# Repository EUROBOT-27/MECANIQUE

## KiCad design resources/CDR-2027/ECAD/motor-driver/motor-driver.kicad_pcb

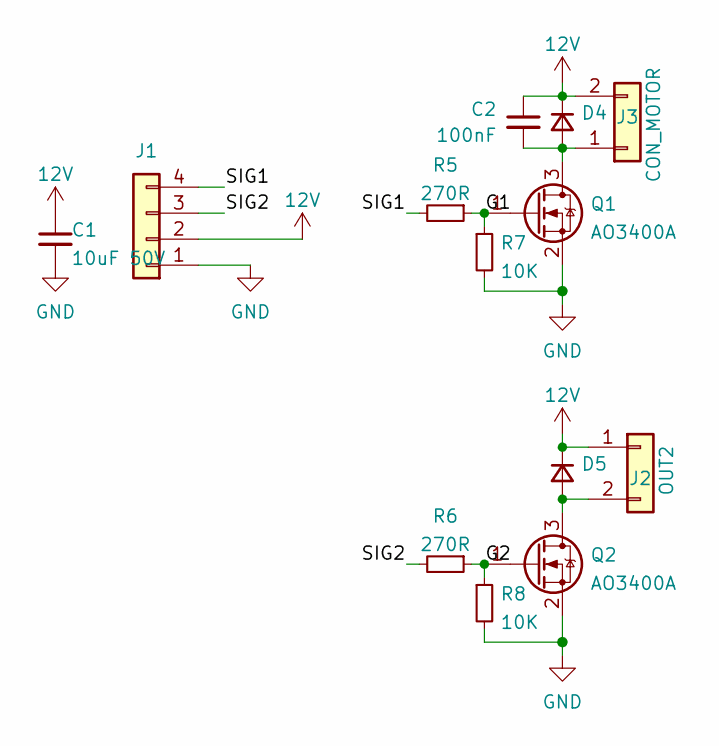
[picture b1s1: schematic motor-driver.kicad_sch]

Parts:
C1: 10uF 50V; C_1206_3216Metric; LCSC C13585
C2: 100nF; C_1206_3216Metric; LCSC C24497
D4, D5: SS34; D_SMA; LCSC C8678
J1: Conn_01x04; Molex_KK-254_AE-6410-04A_1x04_P2.54mm_Vertical
J2: OUT2; Molex_KK-254_AE-6410-02A_1x02_P2.54mm_Vertical
J3: CON_MOTOR; Moteur_Cosses_2xFente_3.6x2.2mm_R10.6mm
Q1, Q2: AO3400A; SOT-23; LCSC C20917
R5, R6: 270R; R_1206_3216Metric; LCSC C4466
R7, R8: 10K; R_1206_3216Metric; LCSC C17902

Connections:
12V: C1.1, C2.1, D4.1 (K), D5.1 (K), J1.2, J2.1, J3.2
/G1: Q1.1 (G), R5.1, R7.1
/G2: Q2.1 (G), R6.1, R8.1
/SIG1: J1.4, R5.2
/SIG2: J1.3, R6.2
GND: C1.2, J1.1, Q1.2 (S), Q2.2 (S), R7.2, R8.2
unnamed: C2.2, D4.2 (A), J3.1, Q1.3 (D)
unnamed: D5.2 (A), J2.2, Q2.3 (D)

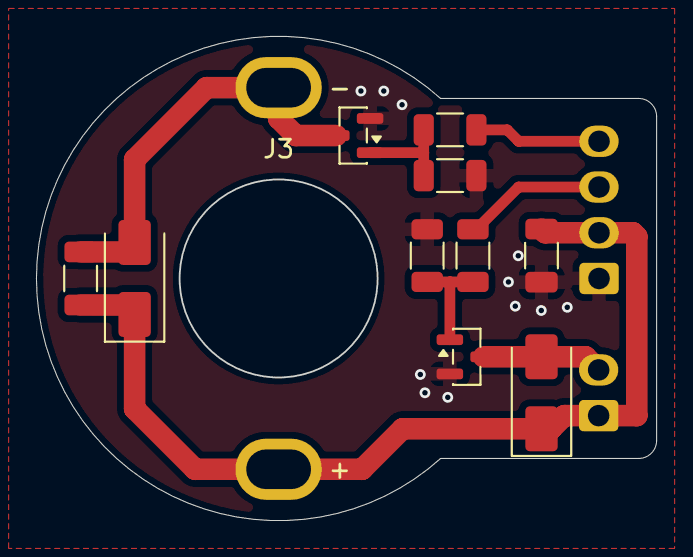
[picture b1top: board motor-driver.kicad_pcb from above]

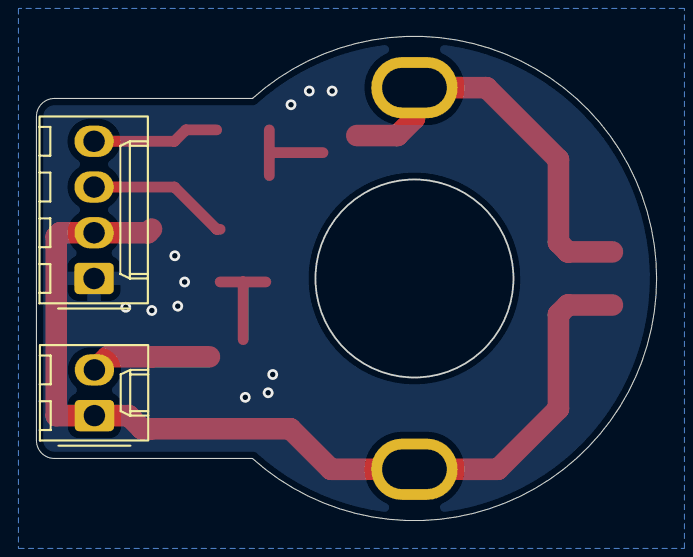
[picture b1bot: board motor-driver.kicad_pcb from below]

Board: 2 copper layers, 34.5 x 26.9 mm, 13 parts (2 on the bottom side), 8 nets.

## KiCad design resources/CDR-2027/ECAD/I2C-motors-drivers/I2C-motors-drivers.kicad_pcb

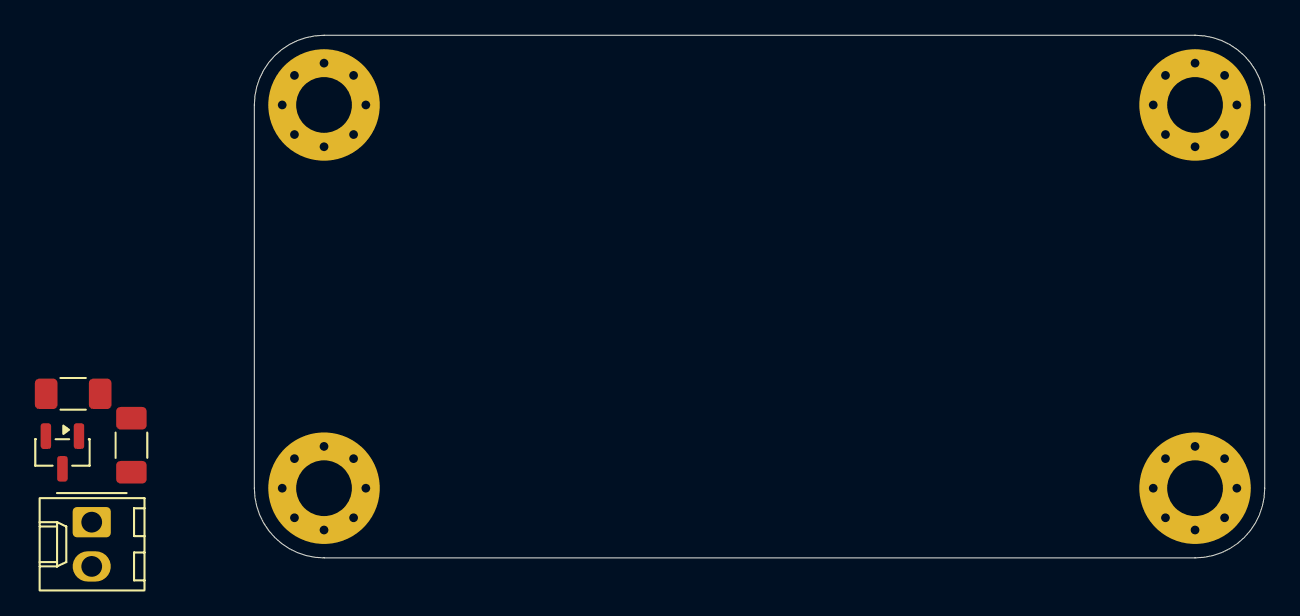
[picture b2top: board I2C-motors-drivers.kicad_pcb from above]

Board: 2 copper layers, 58.0 x 30.0 mm, 9 parts (1 on the bottom side), 4 nets, no tracks yet.

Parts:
D4: D_Small; D_SMA_Handsoldering
H1, H2, H3, H4: MountingHole_Pad_MP; MountingHole_3.2mm_M3_Pad_Via
J3: CON_EV; Molex_KK-254_AE-6410-02A_1x02_P2.54mm_Vertical
Q1: AO3400A; SOT-23
R5: 270R; R_1206_3216Metric_Pad1.30x1.75mm_HandSolder
R7: 10K; R_1206_3216Metric_Pad1.30x1.75mm_HandSolder

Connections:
12V: D4.1 (K), J3.2
GND: Q1.2 (S), R7.2
unnamed: D4.2 (A), J3.1, Q1.3 (D)
unnamed: Q1.1 (G), R5.1, R7.1

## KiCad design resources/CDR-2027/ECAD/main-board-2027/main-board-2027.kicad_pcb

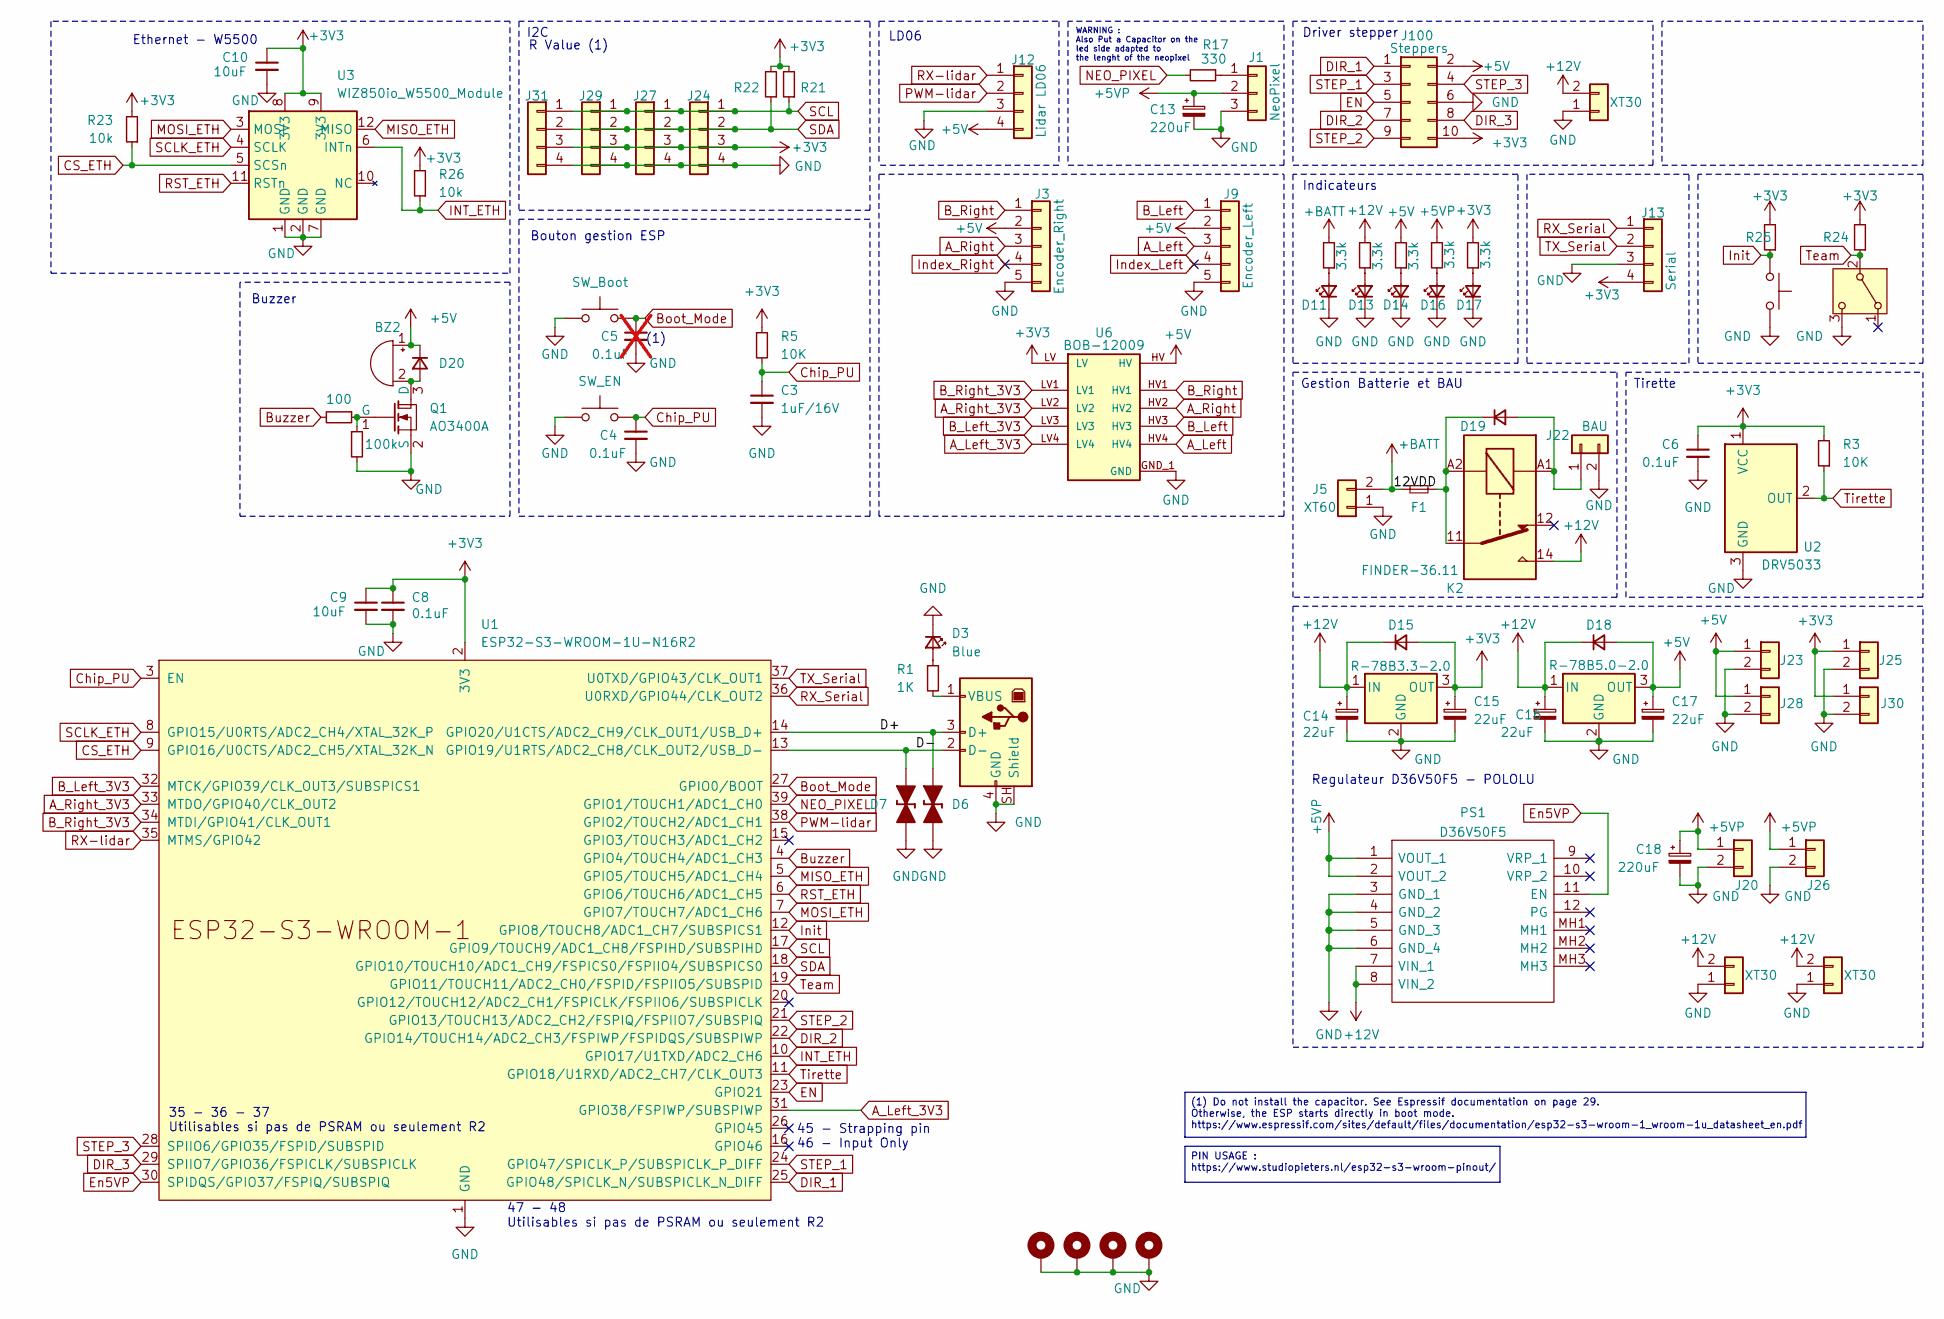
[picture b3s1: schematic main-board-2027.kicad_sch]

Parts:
BZ2: Buzzer; Buzzer_12x9.5RM7.6
C3: 1uF/16V; C_1206_3216Metric
C4: 0.1uF; C_1206_3216Metric
C5: 0.1uF; C_1206_3216Metric; not fitted
C6, C8: 0.1uF; C_1206_3216Metric_Pad1.33x1.80mm_HandSolder
C9, C10: 10uF; C_1206_3216Metric_Pad1.33x1.80mm_HandSolder
C13, C18: 220uF; CP_Radial_D8.0mm_P3.80mm
C14, C15, C16, C17: 22uF; CP_Elec_5x5.4
D3: Blue; LED_1206_3216Metric
D6, D7: D_TVS_Bidirectional_Generic; D_SOD-523
D11, D13, D14, D16, D17: LED_Small; LED_1206_3216Metric_Pad1.42x1.75mm_HandSolder
D15, D18, D19: D_Small; D_SMA_Handsoldering
D20: SS34; D_SMA_Handsoldering
F1: Fuse_Small; Fuseholder_Blade_Mini_Keystone_3568
H5, H6, H7, H8: MountingHole_Pad; MountingHole_3.2mm_M3_Pad_Via
J1: NeoPixel; Molex_KK-254_AE-6410-03A_1x03_P2.54mm_Vertical
J2: USB_B; USB_B_TE_5787834_Vertical
J3: Encoder_Right; Molex_KK-254_AE-6410-05A_1x05_P2.54mm_Vertical
J5: XT60; AMASS_XT60-M_1x02_P7.20mm_Vertical
J9: Encoder_Left; Molex_KK-254_AE-6410-05A_1x05_P2.54mm_Vertical
J12: Lidar LD06; Molex_KK-254_AE-6410-04A_1x04_P2.54mm_Vertical
J13: Serial; Molex_KK-254_AE-6410-04A_1x04_P2.54mm_Vertical
J16, J17, J18: XT30; AMASS_XT30U-F_1x02_P5.0mm_Vertical
J20, J26: Molex_KK-396_A-41791-0002_1x02_P3.96mm_Vertical
J22: BAU; Molex_KK-396_A-41791-0002_1x02_P3.96mm_Vertical
J23, J25, J28, J30: Conn_01x02; Molex_KK-254_AE-6410-02A_1x02_P2.54mm_Vertical
J24, J27, J29, J31: External tools; Molex_KK-254_AE-6410-04A_1x04_P2.54mm_Vertical
J100: Steppers; IDC-Header_2x05_P2.54mm_Vertical
K2: FINDER-36.11; Relay_SPDT_Finder_36.11
PS1: D36V50F5; Manufacturer_Part_Number D36V50F5
Q1: AO3400A; SOT-23_Handsoldering
R1: 1K; R_1206_3216Metric_Pad1.30x1.75mm_HandSolder
R3, R5: 10K; R_1206_3216Metric_Pad1.30x1.75mm_HandSolder
R15, R16, R18, R19, R20: 3.3k; R_1206_3216Metric_Pad1.30x1.75mm_HandSolder
R17: 330; R_1206_3216Metric_Pad1.30x1.75mm_HandSolder
R21, R22: 4.7k; R_1206_3216Metric_Pad1.30x1.75mm_HandSolder
R23, R24, R25, R26: 10k; R_1206_3216Metric_Pad1.30x1.75mm_HandSolder
R27: 100; R_1206_3216Metric_Pad1.30x1.75mm_HandSolder
R28: 100k; R_1206_3216Metric_Pad1.30x1.75mm_HandSolder
SW1: SW_SPDT; SK-12D10 1P2T
SW2: SW_Push; SW_Cherry_MX_PCB
SWBoot1: SW_Boot; SW_SPST_CK_RS282G05A3
SWEn1: SW_EN; SW_SPST_CK_RS282G05A3
U1: ESP32-S3-WROOM-1U-N16R2; ESP32-S3-WROOM-1U
U2: DRV5033; SOT-23_Handsoldering
U3: WIZ850io_W5500_Module
U6: BOB-12009; CONV_BOB-12009; PARTREV 01
U7: R-78B3.3-2.0; Converter_DCDC_RECOM_R-78B-2.0_THT
U8: R-78B5.0-2.0; Converter_DCDC_RECOM_R-78B-2.0_THT

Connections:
+3V3: C6.1, C8.1, C9.1, C10.1, C15.1, D15.2 (A), J13.4, J24.3, J25.1, J27.3, J29.3, J30.1, J31.3, J100.10, R3.2, R5.1, R20.2, R21.2, R22.2, R23.2, R24.2, R25.2, R26.2, U1.2 (3V3), U2.1 (VCC), U3.8 (3V3), U3.9 (3V3), U6.LV, U7.3 (OUT)
+5V: BZ2.1 (+), C17.1, D18.2 (A), D20.1 (K), J3.2, J9.2, J12.4, J23.1, J28.1, J100.2, R18.2, U6.HV, U8.3 (OUT)
+5VP: C13.1, C18.1, J1.2, J20.1, J26.1, PS1.1 (VOUT_1), PS1.2 (VOUT_2), R19.1
+12V: C14.1, C16.1, D15.1 (K), D18.1 (K), J16.2, J17.2, J18.2, K2.14, PS1.7 (VIN_1), PS1.8 (VIN_2), R16.2, U7.1 (IN), U8.1 (IN)
+BATT: F1.1, J5.2, R15.2
/12VDD: D19.1 (K), F1.2, K2.11, K2.A2
/D+: D6.2 (A), J2.3 (D+), U1.14 (GPIO20/U1CTS/ADC2_CH9/CLK_OUT1/USB_D+)
/D-: D7.2 (A), J2.2 (D-), U1.13 (GPIO19/U1RTS/ADC2_CH8/CLK_OUT2/USB_D-)
A_Left: J9.3, U6.HV4
A_Left_3V3: U1.31 (GPIO38/FSPIWP/SUBSPIWP), U6.LV4
A_Right: J3.3, U6.HV2
A_Right_3V3: U1.33 (MTDO/GPIO40/CLK_OUT2), U6.LV2
B_Left: J9.1, U6.HV3
B_Left_3V3: U1.32 (MTCK/GPIO39/CLK_OUT3/SUBSPICS1), U6.LV3
B_Right: J3.1, U6.HV1
B_Right_3V3: U1.34 (MTDI/GPIO41/CLK_OUT1), U6.LV1
Boot_Mode: C5.1, SWBoot1.2, U1.27 (GPIO0/BOOT)
Buzzer: R27.2, U1.4 (GPIO4/TOUCH4/ADC1_CH3)
CS_ETH: R23.1, U1.9 (GPIO16/U0CTS/ADC2_CH5/XTAL_32K_N), U3.5 (SCSn)
Chip_PU: C3.1, C4.1, R5.2, SWEn1.2, U1.3 (EN)
DIR_1: J100.1, U1.25 (GPIO48/SPICLK_N/SUBSPICLK_N_DIFF)
DIR_2: J100.7, U1.22 (GPIO14/TOUCH14/ADC2_CH3/FSPIWP/FSPIDQS/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)
DIR_3: J100.8, U1.29 (SPIIO7/GPIO36/FSPICLK/SUBSPICLK)
EN: J100.5, U1.23 (GPIO21)
En5VP: PS1.11 (EN), U1.30 (SPIDQS/GPIO37/FSPIQ/SUBSPIQ)
GND: C3.2, C4.2, C5.2, C6.2, C8.2, C9.2, C10.2, C13.2, C14.2, C15.2, C16.2, C17.2, C18.2, D3.1 (K), D6.1 (K), D7.1 (K), D11.1 (K), D13.1 (K), D14.1 (K), D16.1 (K), D17.1 (K), H5.1 (1_1), H6.1 (1_1), H7.1 (1_1), H8.1 (1_1), J1.3, J2.4 (GND), J2.SH (Shield), J3.5, J5.1, J9.5, J12.3, J13.3, J16.1, J17.1, J18.1, J20.2, J22.2, J23.2, J24.4, J25.2, J26.2, J27.4, J28.2, J29.4, J30.2, J31.4, J100.6, PS1.3 (GND_1), PS1.4 (GND_2), PS1.5 (GND_3), PS1.6 (GND_4), Q1.2 (S), R28.2, SW1.3 (C), SW2.2, SWBoot1.1, SWEn1.1, U1.1 (GND), U1.40 (GND), U1.41 (GND), U2.3 (GND), U3.1 (GND), U3.2 (GND), U3.7 (GND), U6.GND_1 (GND), U6.GND_2 (GND), U7.2 (GND), U8.2 (GND)
INT_ETH: R26.1, U1.10 (GPIO17/U1TXD/ADC2_CH6), U3.6 (INTn)
Index_Left: J9.4
Index_Right: J3.4
Init: R25.1, SW2.1, U1.12 (GPIO8/TOUCH8/ADC1_CH7/SUBSPICS1)
MISO_ETH: U1.5 (GPIO5/TOUCH5/ADC1_CH4), U3.12 (MISO)
MOSI_ETH: U1.7 (GPIO7/TOUCH7/ADC1_CH6), U3.3 (MOSI)
NEO_PIXEL: R17.2, U1.39 (GPIO1/TOUCH1/ADC1_CH0)
unnamed: BZ2.2 (-), D20.2 (A), Q1.3 (D)
unnamed: D3.2 (A), R1.1
unnamed: D11.2 (A), R15.1
unnamed: D13.2 (A), R16.1
unnamed: D14.2 (A), R18.1
unnamed: D16.2 (A), R19.2
unnamed: D17.2 (A), R20.1
unnamed: D19.2 (A), J22.1, K2.A1
unnamed: J1.1, R17.1
unnamed: J2.1 (VBUS), R1.2
unnamed: Q1.1 (G), R27.1, R28.1
PWM-lidar: J12.2, U1.38 (GPIO2/TOUCH2/ADC1_CH1)
RST_ETH: U1.6 (GPIO6/TOUCH6/ADC1_CH5), U3.11 (RSTn)
RX-lidar: J12.1, U1.35 (MTMS/GPIO42)
RX_Serial: J13.1, U1.36 (U0RXD/GPIO44/CLK_OUT2)
SCL: J24.1, J27.1, J29.1, J31.1, R21.1, U1.17 (GPIO9/TOUCH9/ADC1_CH8/FSPIHD/SUBSPIHD)
SCLK_ETH: U1.8 (GPIO15/U0RTS/ADC2_CH4/XTAL_32K_P), U3.4 (SCLK)
SDA: J24.2, J27.2, J29.2, J31.2, R22.1, U1.18 (GPIO10/TOUCH10/ADC1_CH9/FSPICS0/FSPIIO4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)
STEP_1: J100.3, U1.24 (GPIO47/SPICLK_P/SUBSPICLK_P_DIFF)
STEP_2: J100.9, U1.21 (GPIO13/TOUCH13/ADC2_CH2/FSPIQ/FSPIIO7/S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)
STEP_3: J100.4, U1.28 (SPIIO6/GPIO35/FSPID/SUBSPID)
TX_Serial: J13.2, U1.37 (U0TXD/GPIO43/CLK_OUT1)
Team: R24.1, SW1.2 (B), U1.19 (GPIO11/TOUCH11/ADC2_CH0/FSPID/FSPIIO5/S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)
Tirette: R3.1, U1.11 (GPIO18/U1RXD/ADC2_CH7/CLK_OUT3), U2.2 (OUT)

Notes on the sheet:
WARNING : Also Put a Capacitor on the led side adapted to the lenght of the neopixel
R Value (1)
Buzzer
I2C
Gestion Batterie et BAU
Ethernet - W5500
35 - 36 - 37 Utilisables si pas de PSRAM ou seulement R2
Bouton gestion ESP
Tirette
(1)
LD06
47 - 48 Utilisables si pas de PSRAM ou seulement R2
Indicateurs
45 - Strapping pin 46 - Input Only
Regulateur D36V50F5 - POLOLU
Driver stepper
PIN USAGE : https://www.studiopieters.nl/esp32-s3-wroom-pinout/
(1) Do not install the capacitor. See Espressif documentation on page 29. Otherwise, the ESP starts directly in boot mode. https://www.espressif.com/sites/default/files/documentation/esp32-s3-wroom-1_wroom-1u_datasheet_en.pdf

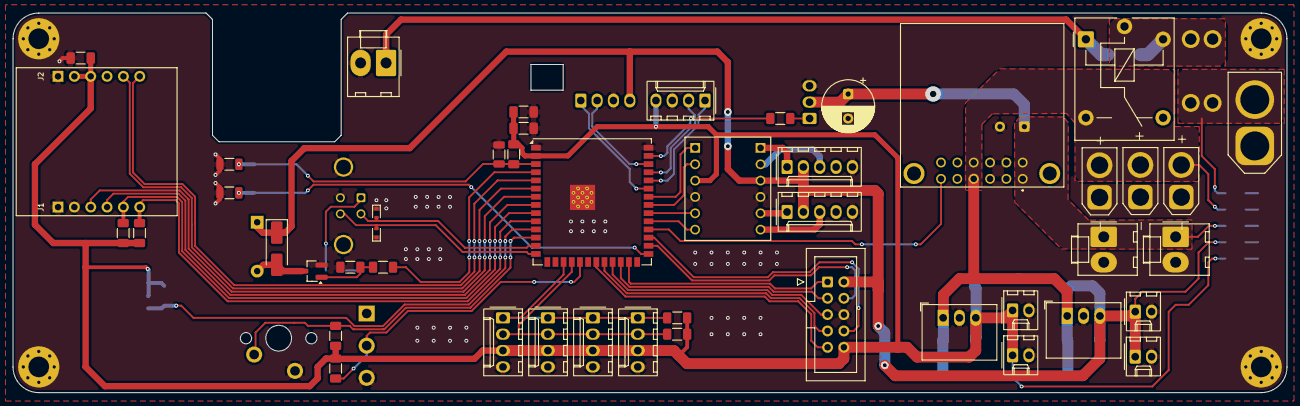
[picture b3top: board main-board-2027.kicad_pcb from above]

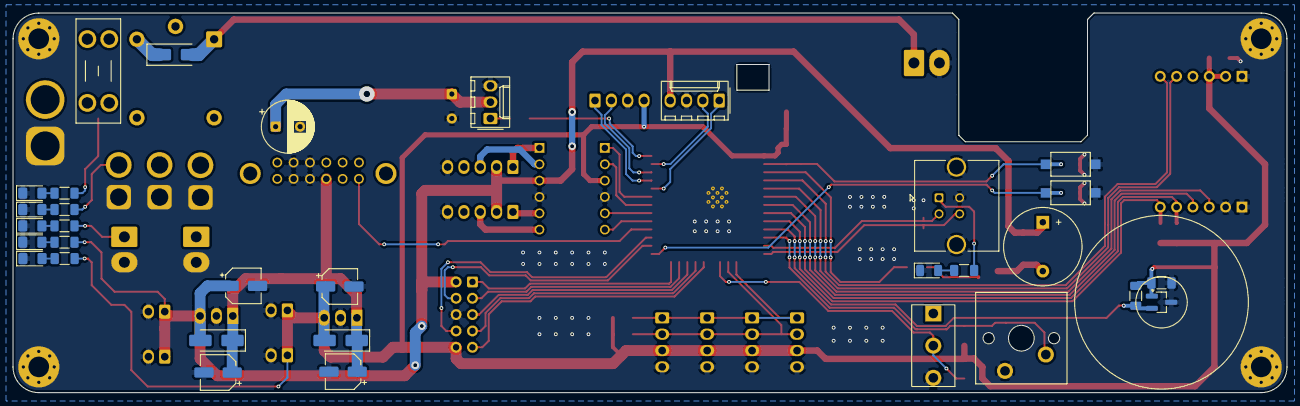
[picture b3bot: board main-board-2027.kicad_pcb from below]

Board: 2 copper layers, 198.0 x 59.0 mm, 83 parts (32 on the bottom side), 55 nets.

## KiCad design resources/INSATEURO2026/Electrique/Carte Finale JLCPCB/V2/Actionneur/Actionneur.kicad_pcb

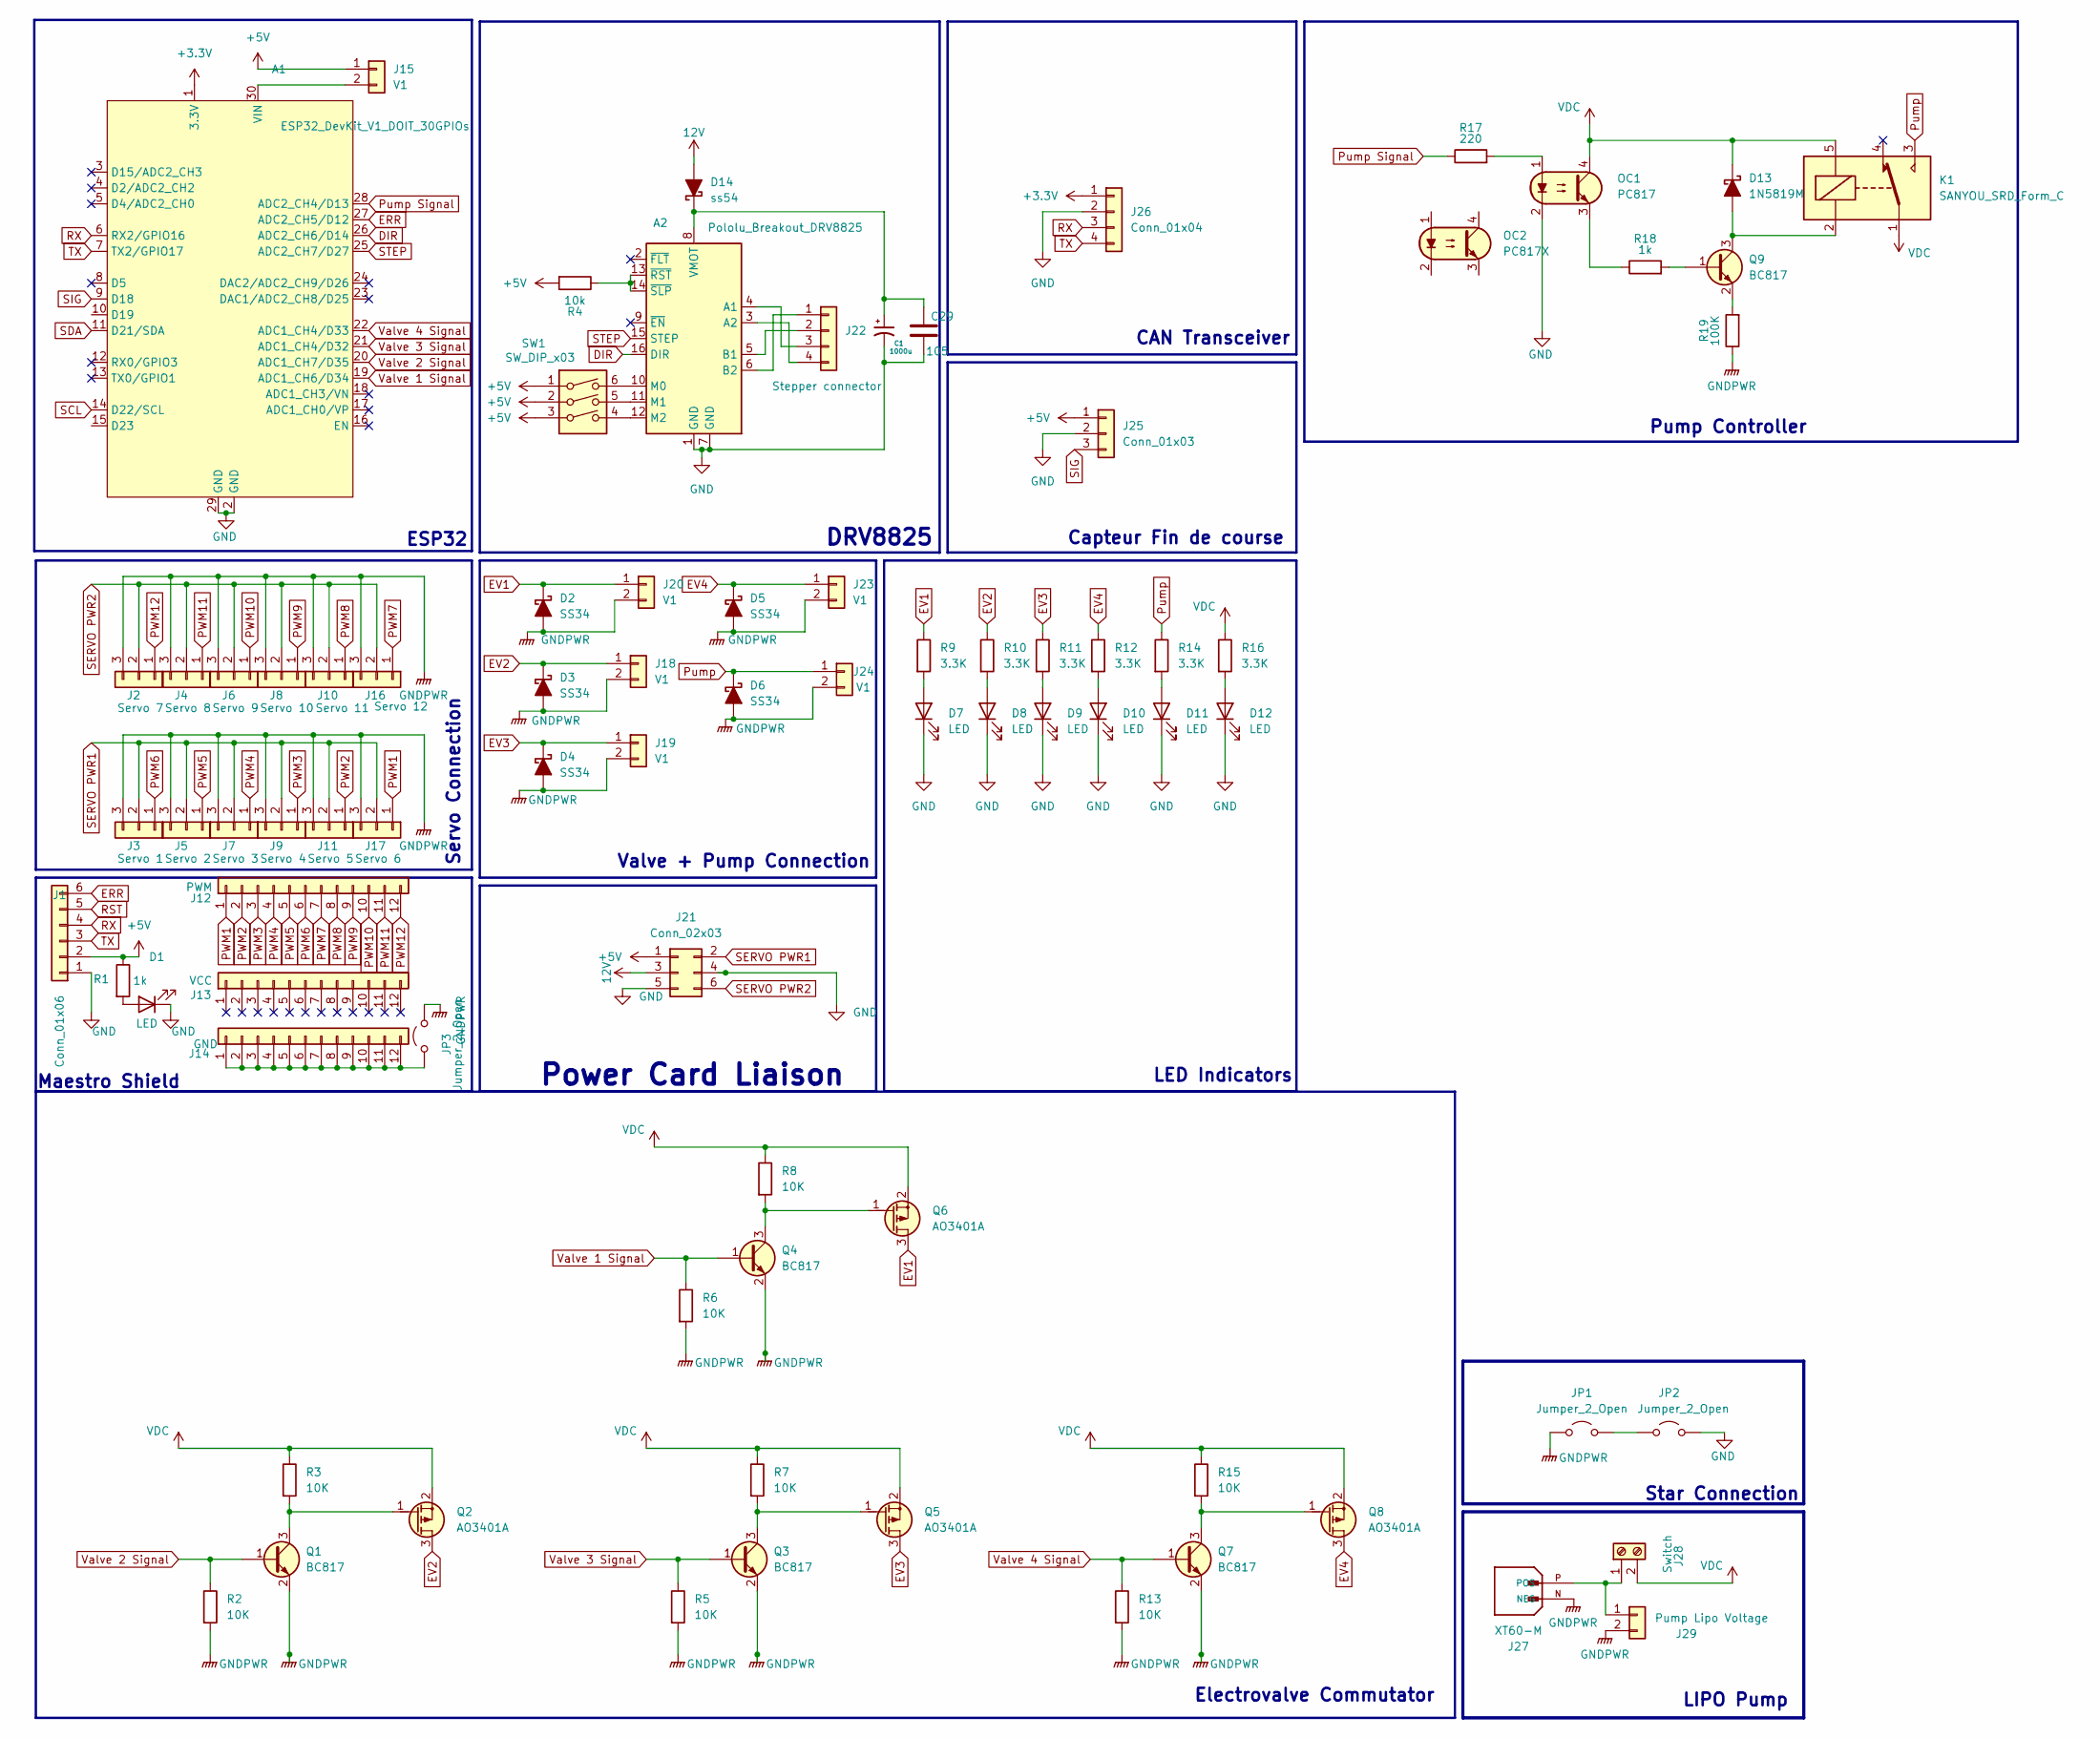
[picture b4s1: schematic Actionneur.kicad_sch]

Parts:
A1: ESP32_DevKit_V1_DOIT_30GPIOs; DOIT_ESP32_DEVKIT_30Pins
A2: Pololu_Breakout_DRV8825; Pololu_Breakout-16_15.2x20.3mm
C1: 1000u; CP_Elec_10x10.5
C29: 105; C_0603_1608Metric
D1, D7, D8, D9, D10, D11, D12: LED; LED_0603_1608Metric
D2, D3, D4, D5, D6: SS34; D_SOD-323
D13: 1N5819M; D_SMC
D14: ss54; D_SOD-323
J1: Conn_01x06; PinSocket_1x06_P2.54mm_Vertical
J2: Servo 7; PinHeader_1x03_P2.54mm_Vertical
J3: Servo 1; PinHeader_1x03_P2.54mm_Vertical
J4: Servo 8; PinHeader_1x03_P2.54mm_Vertical
J5: Servo 2; PinHeader_1x03_P2.54mm_Vertical
J6: Servo 9; PinHeader_1x03_P2.54mm_Vertical
J7: Servo 3; PinHeader_1x03_P2.54mm_Vertical
J8: Servo 10; PinHeader_1x03_P2.54mm_Vertical
J9: Servo 4; PinHeader_1x03_P2.54mm_Vertical
J10: Servo 11; PinHeader_1x03_P2.54mm_Vertical
J11: Servo 5; PinHeader_1x03_P2.54mm_Vertical
J12: PWM; PinSocket_1x12_P2.54mm_Vertical
J13: VCC; PinSocket_1x12_P2.54mm_Vertical
J14: GND; PinSocket_1x12_P2.54mm_Vertical
J15, J18, J19, J20, J23, J24: V1; JST_PH_B2B-PH-K_1x02_P2.00mm_Vertical
J16: Servo 12; PinHeader_1x03_P2.54mm_Vertical
J17: Servo 6; PinHeader_1x03_P2.54mm_Vertical
J21: Conn_02x03; Molex_Mini-Fit_Jr_5566-06A_2x03_P4.20mm_Vertical
J22: Stepper connector; JST_EH_B4B-EH-A_1x04_P2.50mm_Vertical
J25: Conn_01x03; JST_EH_B3B-EH-A_1x03_P2.50mm_Vertical
J26: Conn_01x04; JST_EH_B4B-EH-A_1x04_P2.50mm_Vertical
J27: XT60-M; AMASS_XT60-M; PARTREV V1.2
J28: Switch; TerminalBlock_Phoenix_MKDS-1,5-2-5.08_1x02_P5.08mm_Horizont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
J29: Pump Lipo Voltage; JST_PH_B2B-PH-K_1x02_P2.00mm_Vertical
JP1, JP2, JP3: Jumper_2_Open; Jumper_P2.54mm_D0.7mm
K1: SANYOU_SRD_Form_C; Relay_SPDT_SANYOU_SRD_Series_Form_C
OC1: PC817; Vishay_CNY64
OC2: PC817X; DIP-4_W7.62mm_LongPads
Q1, Q3, Q4, Q7, Q9: BC817; SOT-23
Q2, Q5, Q6, Q8: AO3401A; SOT-23
R1, R18: 1k; R_0603_1608Metric
R2, R3, R5, R6, R7, R8, R13, R15: 10K; R_0603_1608Metric
R4: 10k; R_0603_1608Metric
R9, R10, R11, R12, R14, R16: 3.3K; R_0603_1608Metric
R17: 220; R_0603_1608Metric
R19: 100K; R_0603_1608Metric
SW1: SW_DIP_x03; SW_DIP_SPSTx03_Slide_6.7x9.18mm_W6.73mm_P2.54mm_LowProfile_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

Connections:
12V: D14.2 (A), J21.3
+3.3V: A1.1 (3.3V), J26.1
+5V: J1.2, J15.1, J21.1, J25.1, R1.1, R4.2, SW1.1, SW1.2, SW1.3
Alt Pump: K1.4
DIR: A1.26 (ADC2_CH6/D14), A2.16 (DIR)
ERR: A1.27 (ADC2_CH5/D12), J1.6
EV1: D2.1 (K), J20.1, Q6.3 (D), R9.1
EV2: D3.1 (K), J18.1, Q2.3 (D), R10.1
EV3: D4.1 (K), J19.1, Q5.3 (D), R11.1
EV4: D5.1 (K), J23.1, Q8.3 (D), R12.1
GND: A1.2 (GND), A1.29 (GND), A2.1 (GND), A2.7 (GND), C1.2, C29.2, D1.1 (K), D7.1 (K), D8.1 (K), D9.1 (K), D10.1 (K), D11.1 (K), D12.1 (K), J1.1, J21.4, J21.5, J25.2, J26.2, JP2.2 (B), OC1.2
GNDPWR: D2.2 (A), D3.2 (A), D4.2 (A), D5.2 (A), D6.2 (A), J2.3, J3.3, J4.3, J5.3, J6.3, J7.3, J8.3, J9.3, J10.3, J11.3, J16.3, J17.3, J18.2, J19.2, J20.2, J23.2, J24.2, J27.N (NEG), J29.2, JP1.1 (A), JP3.2 (B), Q1.2 (E), Q3.2 (E), Q4.2 (E), Q7.2 (E), R2.2, R5.2, R6.2, R13.2, R19.1
unnamed: A1.30 (VIN), J15.2
unnamed: A2.4 (A1), J22.3
unnamed: A2.3 (A2), J22.4
unnamed: A2.5 (B1), J22.2
unnamed: A2.6 (B2), J22.1
unnamed: A2.10 (M0), SW1.6
unnamed: A2.11 (M1), SW1.5
unnamed: A2.12 (M2), SW1.4
unnamed: A2.8 (VMOT), C1.1, C29.1, D14.1 (K)
unnamed: A2.13 (~RST), A2.14 (~SLP), R4.1
unnamed: D1.2 (A), R1.2
unnamed: D7.2 (A), R9.2
unnamed: D8.2 (A), R10.2
unnamed: D9.2 (A), R11.2
unnamed: D10.2 (A), R12.2
unnamed: D11.2 (A), R14.2
unnamed: D12.2 (A), R16.2
unnamed: D13.2 (A), K1.2, Q9.3 (C)
unnamed: J14.1, J14.2, J14.3, J14.4, J14.5, J14.6, J14.7, J14.8, J14.9, J14.10, J14.11, J14.12, JP3.1 (A)
unnamed: J27.P (POS), J28.1, J29.1
unnamed: JP1.2 (B), JP2.1 (A)
unnamed: OC1.1, R17.2
unnamed: OC1.3, R18.1
unnamed: Q1.3 (C), Q2.1 (G), R3.2
unnamed: Q3.3 (C), Q5.1 (G), R7.2
unnamed: Q4.3 (C), Q6.1 (G), R8.2
unnamed: Q7.3 (C), Q8.1 (G), R15.2
unnamed: Q9.1 (B), R18.2
unnamed: Q9.2 (E), R19.2
PWM1: J12.1, J17.1
PWM2: J11.1, J12.2
PWM3: J9.1, J12.3
PWM4: J7.1, J12.4
PWM5: J5.1, J12.5
PWM6: J3.1, J12.6
PWM7: J12.7, J16.1
PWM8: J10.1, J12.8
PWM9: J8.1, J12.9
PWM10: J6.1, J12.10
PWM11: J4.1, J12.11
PWM12: J2.1, J12.12
Pump: D6.1 (K), J24.1, K1.3, R14.1
Pump Signal: A1.28 (ADC2_CH4/D13), R17.1
RST: J1.5
RX: A1.6 (RX2/GPIO16), J1.4, J26.3
SCL: A1.14 (D22/SCL)
SDA: A1.11 (D21/SDA)
SERVO PWR1: J3.2, J5.2, J7.2, J9.2, J11.2, J17.2, J21.2
SERVO PWR2: J2.2, J4.2, J6.2, J8.2, J10.2, J16.2, J21.6
SIG: A1.9 (D18), J25.3
STEP: A1.25 (ADC2_CH7/D27), A2.15 (STEP)
TX: A1.7 (TX2/GPIO17), J1.3, J26.4
VDC: D13.1 (K), J28.2, K1.1, K1.5, OC1.4, Q2.2 (S), Q5.2 (S), Q6.2 (S), Q8.2 (S), R3.1, R7.1, R8.1, R15.1, R16.1
Valve 1 Signal: A1.19 (ADC1_CH6/D34), Q4.1 (B), R6.1
Valve 2 Signal: A1.20 (ADC1_CH7/D35), Q1.1 (B), R2.1
Valve 3 Signal: A1.21 (ADC1_CH4/D32), Q3.1 (B), R5.1
Valve 4 Signal: A1.22 (ADC1_CH4/D33), Q7.1 (B), R13.1

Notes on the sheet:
LED Indicators
ESP32
LIPO Pump
Valve + Pump Connection
Star Connection
CAN Transceiver
Maestro Shield
Electrovalve Commutator
DRV8825
Pump Controller
Power Card Liaison
Servo Connection
Capteur Fin de course

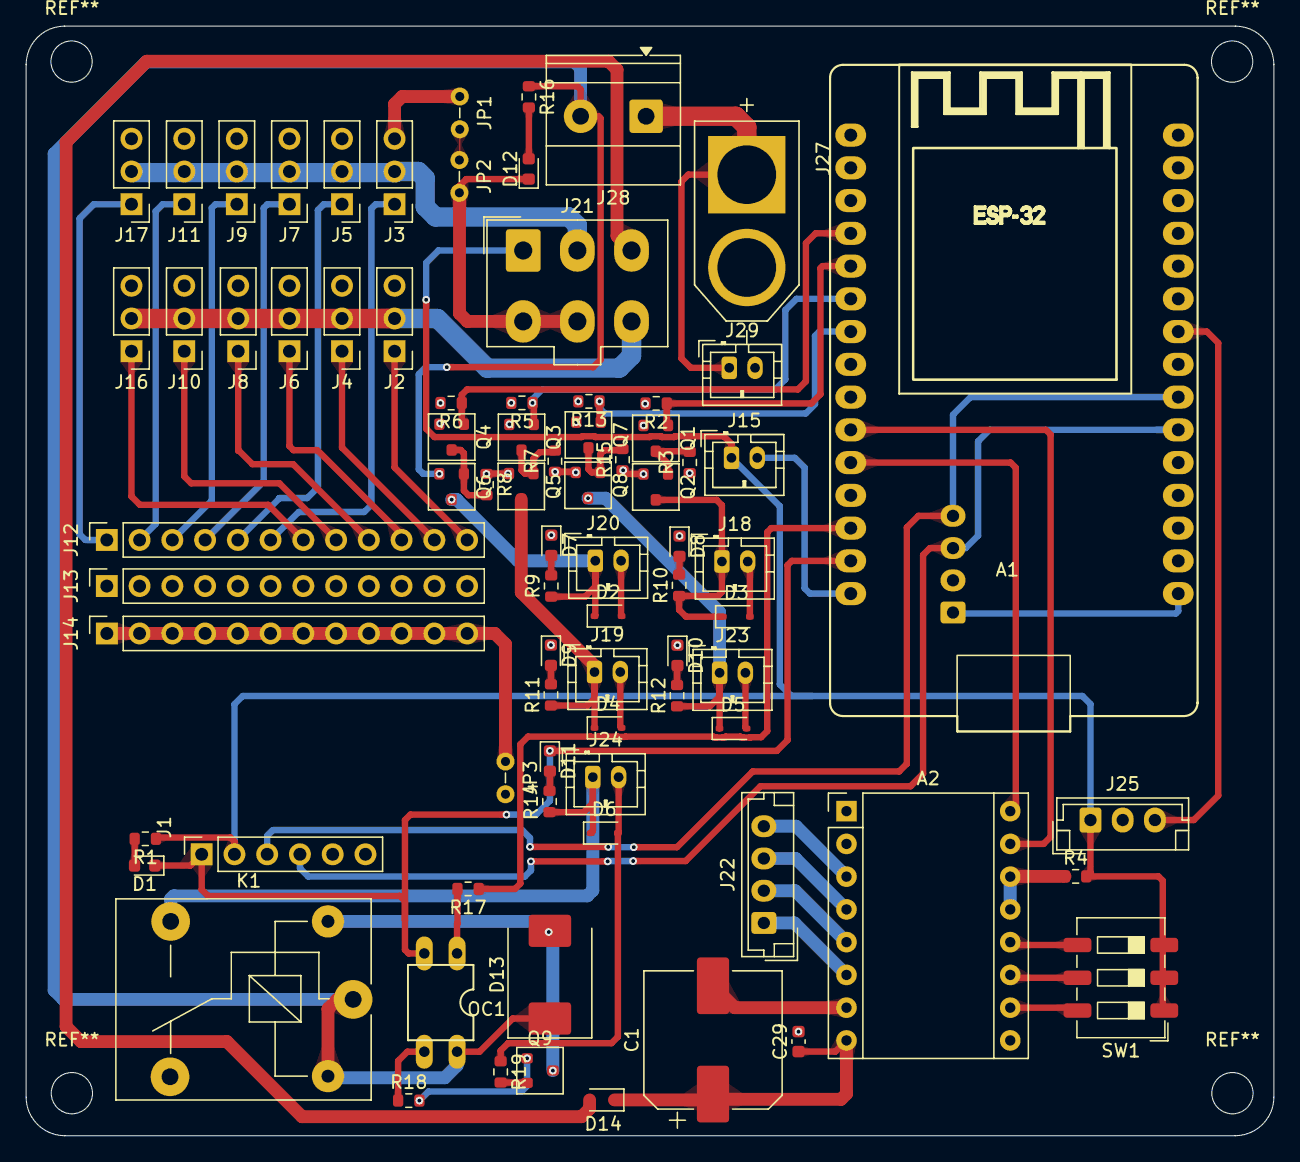
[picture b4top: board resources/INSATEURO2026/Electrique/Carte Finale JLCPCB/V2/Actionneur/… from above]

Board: 4 copper layers, 96.8 x 86.1 mm, 81 parts (1 on the bottom side), 65 nets.
